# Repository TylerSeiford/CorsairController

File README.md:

# CorsairController
This is the code and kicad files for my knock off Corsair CommanderPRO using an ATmega32u4 microcontroller.

## Hardware
This uses an ATmega32u4 microcontroller to control addressable and non addressable LED strips, along with 3 and 4 pin DC fans.  It utilizes the [CorsairLightingProtocol](https://github.com/Legion2/CorsairLightingProtocol) and builds on top of it to add additional functionality.

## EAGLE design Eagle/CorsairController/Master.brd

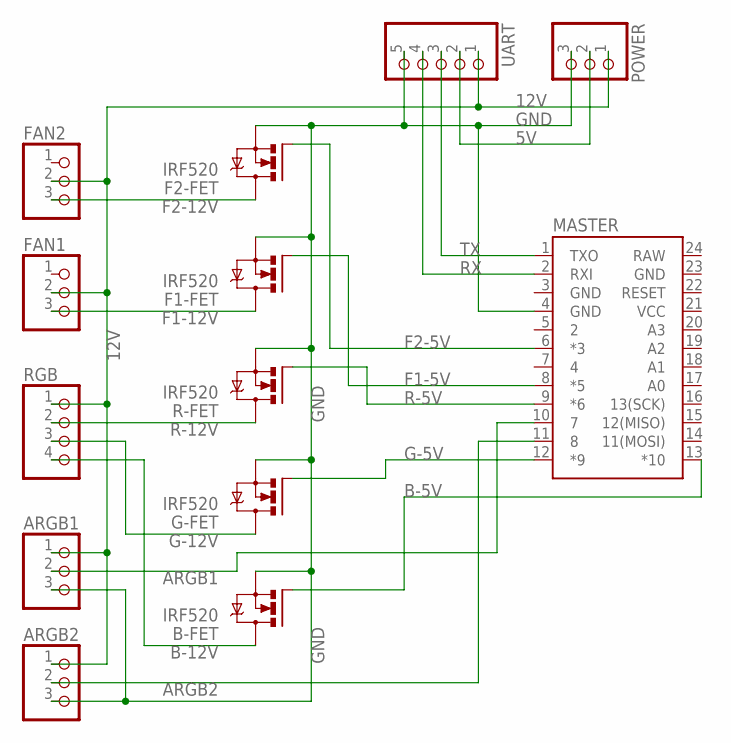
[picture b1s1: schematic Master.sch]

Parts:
ARGB1, ARGB2: PINHD-1X3/90; 1X03/90
B-FET: IRF520; TO220BV
F1-FET, F2-FET: IRF520; TO220BV
FAN1, FAN2: PINHD-1X3/90; 1X03/90
G-FET: IRF520; TO220BV
MASTER: SPARKFUN_PRO_MICRO
POWER: PINHD-1X3/90; 1X03/90
R-FET: IRF520; TO220BV
RGB: PINHD-1X4/90; 1X04/90
UART: PINHD-1X5/90; 1X05/90

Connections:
5V: POWER.2, UART.2
12V: ARGB1.1, ARGB2.1, FAN1.2, FAN2.2, POWER.1, RGB.1, UART.1
ARGB1: ARGB1.2, MASTER.10 (7)
ARGB2: ARGB2.2, MASTER.11 (8)
B-5V: B-FET.G, MASTER.13 (*10)
B-12V: B-FET.D, RGB.4
F1-5V: F1-FET.G, MASTER.8 (*5)
F1-12V: F1-FET.D, FAN1.3
F2-5V: F2-FET.G, MASTER.6 (*3)
F2-12V: F2-FET.D, FAN2.3
G-5V: G-FET.G, MASTER.12 (*9)
G-12V: G-FET.D, RGB.3
GND: ARGB1.3, ARGB2.3, B-FET.S, F1-FET.S, F2-FET.S, G-FET.S, MASTER.3 (GND), MASTER.4 (GND), MASTER.23 (GND), POWER.3, R-FET.S, UART.5
R-5V: MASTER.9 (*6), R-FET.G
R-12V: R-FET.D, RGB.2
RAW: MASTER.24 (RAW)
RX: MASTER.2 (RXI), UART.4
TX: MASTER.1 (TXO), UART.3
VCC: MASTER.21 (VCC)

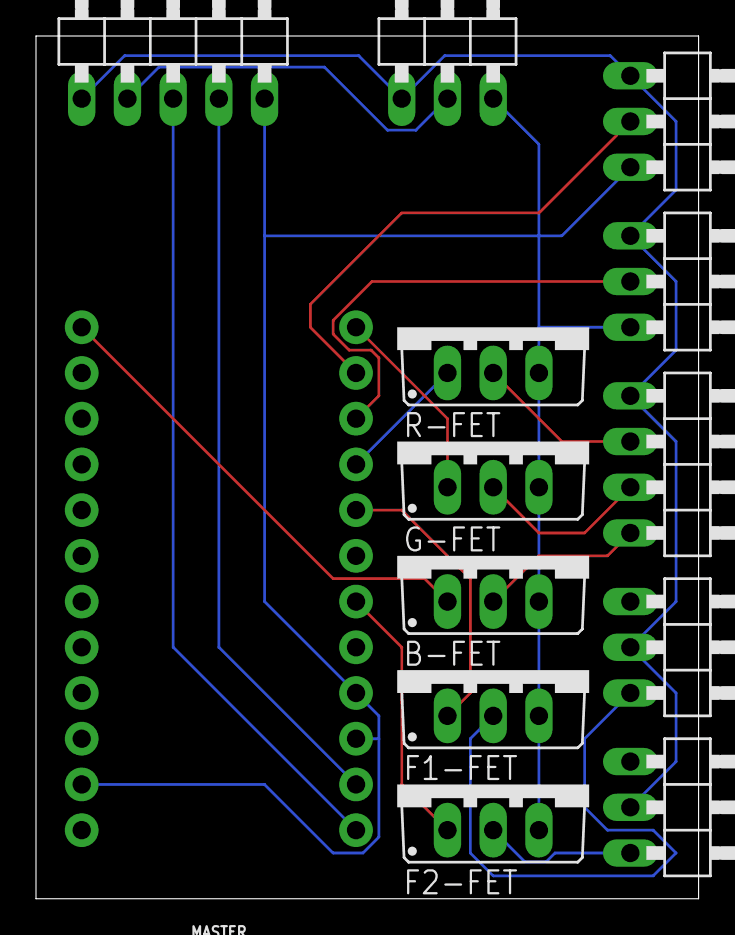
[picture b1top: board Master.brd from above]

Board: 2 copper layers, 36.8 x 47.9 mm, 13 parts (0 on the bottom side), 17 nets.

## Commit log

2019-06-04 Basic lighting node pro class
2019-06-08 Added fritzing files
2019-06-11 Wiring update
2019-06-20 Rename files
2019-06-20 Change pins
2019-06-20 Creating fake temperature controller
2019-06-20 PWM fan
2019-06-20 Simple fan controller
2019-06-20 Commander pro updates
2019-06-20 Inline default update rate
2019-06-20 Update ino
2019-06-20 Fan interface update
2019-06-20 Add fan control to commander pro
2019-06-20 Fix board.txt to commander pro IDs
2019-06-20 Fix detection types
2019-06-20 Working fan control
2019-06-21 Switch to a template system
2019-06-21 Create DC fan
2019-06-22 Updated wiring to dual controller layout
    The second controller is unneeded at the moment but may become useful for full fan control
2019-06-23 Switching to eagle
2019-06-23 Added schematic and board images
2019-08-15 Pin changes, fixing template issues, added switches for 3 or 4 pin mode
2019-08-15 Last eagle revision & updated readme
2019-08-15 Removed eagle & fritzing, updated gitignore for KiCad
2019-08-15 PCB v0.1.0
    Initial kicad upload. This PCB has been a WIP for a while and this is the first time I've uploaded it to github.
2019-08-15 PCB v0.1.1
2019-08-15 PCB v0.1.2
2019-08-15 PCB v0.1.3
    Fixes fan header pinouts
2019-08-15 Redo PCB layout to be more efficient.
2019-08-15 Fix upload
2019-08-15 PCB v0.1.4
    Upload gerbers of first production run!
2019-08-18 Added LICENSE
2019-08-18 Small updates & added photos
2019-08-23 Update software to new CLP library version
2019-08-23 PCB v0.1.5
2019-08-24 Final updates of 2f/2x2argb/1rgb
2019-08-24 Small edits
2019-08-24 Starts of full fan control module
2019-08-24 Fan board is partially complete
2019-08-25 PCB v0.1.6
    Next step will be a complete reorganization of the PCB
2019-08-25 PCB v0.1.7
2019-08-25 Adding SOT-223 footprint from master
2019-08-25 Fan controller v0.0.2
2019-08-25 Fan PCB v0.0.3
2019-08-27 Fan PCB v0.0.4
    Switched to a molex screw terminal input
2019-08-27 PCB v0.1.8
    Switched to a molex screw terminal input
2019-08-27 Moved files
2019-08-27 Cleaned up the merge
2019-08-27 Added molex power input
2019-08-27 Fan PCB v0.0.5
2019-08-27 PCB v0.1.9
2019-08-27 PCB v0.1.9 (reupload)
2019-08-27 Fan PCB v0.0.6
2019-08-28 PCB v0.1.10
2019-08-29 Added reset button footprint & symbol
2019-08-29 PCB v0.1.11
2019-08-29 Fan PCB v0.0.7
2019-08-29 Renaming footprints
2019-08-29 Updated main PCB with new footprint names
2019-08-29 Rename and update fan PCB
2019-08-31 Switch to WS2112B strips
2019-08-31 Fix footprint to be 3"x2"
2019-10-01 Small updates
2019-10-18 Change resistors to 1206 from 0805
    Fan control v0.0.8
2019-11-09 Controller rev 0.2.0
2019-11-09 Remove gerbers
2019-11-09 FanController rev 0.1.0
2019-11-10 Added FET-Breakout PCB
2019-12-16 Moving to bare ATmega32U4 vs Pro Micro
2019-12-21 Small cleanup
2019-12-28 PCB v0.2.2
    Small cleanup, silkscreen work. Still need to do reset button.
2019-12-28 Cleanup of files
2019-12-28 Moved Software into SW folder
2019-12-28 Move KiCad files
2020-01-01 v0.2.5
    Serial number location
2020-01-03 v0.3.0

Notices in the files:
parts and their libraries:
SparkFun-Boards: Licensing: Creative Commons ShareAlike 4.0 International - https://creativecommons.org/licenses/by-sa/4.0
